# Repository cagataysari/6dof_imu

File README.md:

# README #

This is my hobby 6 DOF IMU project.
I am gonna add BOM list, pdf files later.

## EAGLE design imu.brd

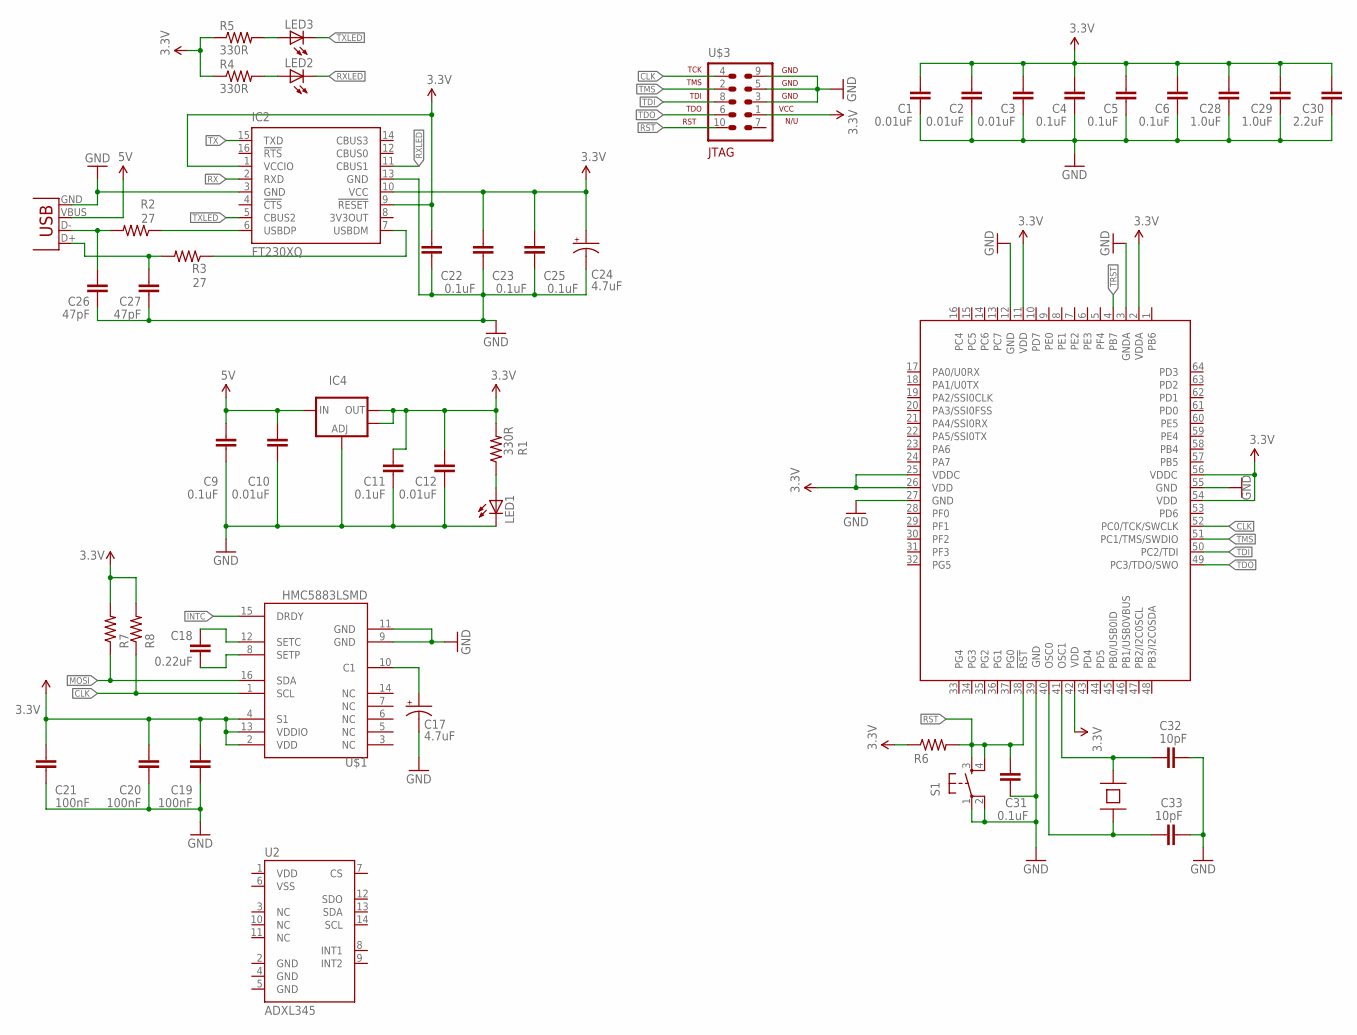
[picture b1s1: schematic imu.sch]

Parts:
C1, C2, C3, C10, C12: 0.01uF; 0603-CAP
C4, C5, C6, C9, C11, C22, C23, C25, C31: 0.1uF; 0603-CAP
C17, C24: 4.7uF; EIA3216
C18: 0.22uF; 0603-CAP
C19, C20, C21: 100nF; 0603-CAP
C26, C27: 47pF; 0603-CAP
C28, C29: 1.0uF; 0603-CAP
C30: 2.2uF; 0603-CAP
C32, C33: 10pF; 0603-CAP
IC1: TM4C123[6,F]XXPM; PM_S-PQFP-G64
IC2: FT230XQ; QFN16
IC4: V_REG_LM1117SOT223; SOT223
JP1: USBSMD; USB-MINIB
LED1, LED2, LED3: LED0603; LED-0603
R1: 330R; 0805
R2, R3: 27; 0603-RES
R4, R5: 330R; 0603-RES
R6, R7, R8: RESISTOR0603-RES; 0603-RES
S1: TAC_SWITCHSMD; TACTILE_SWITCH_SMD
U2: ADXL345; LGA14
U$1: HMC5883LSMD; 16LPCC
U$2: SMDCRYSTAL3225; IQG3225
U$3: ARM10JTAG; AVR-JTAG-10

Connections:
3.3V: C1.2, C2.2, C3.2, C4.2, C5.2, C6.2, C11.2, C12.2, C19.2, C20.2, C21.2, C22.2, C23.2, C24.A (+), C25.2, C28.2, C29.2, C30.2, IC1.2 (VDDA), IC1.11 (VDD), IC1.25 (VDDC), IC1.26 (VDD), IC1.42 (VDD), IC1.54 (VDD), IC1.56 (VDDC), IC2.1 (VCCIO), IC2.9 (!RESET), IC2.10 (VCC), IC4.2 (OUT), IC4.4 (OUT), R1.2, R4.1, R5.1, R6.1, R7.2, R8.2, U$1.2 (VDD), U$1.4 (S1), U$1.13 (VDDIO), U$3.1
5V: C9.2, C10.2, IC4.3 (IN), JP1.VBUS
CLK: IC1.52 (PC0/TCK/SWCLK), R8.1, U$1.1 (SCL), U$3.4
GND: C1.1, C2.1, C3.1, C4.1, C5.1, C6.1, C9.1, C10.1, C11.1, C12.1, C17.C (-), C19.1, C20.1, C21.1, C22.1, C23.1, C24.C (-), C25.1, C26.1, C27.1, C28.1, C29.1, C30.1, C31.1, C32.1, C33.2, IC1.3 (GNDA), IC1.12 (GND), IC1.27 (GND), IC1.39 (GND), IC1.55 (GND), IC2.3 (GND), IC2.13 (GND), IC4.1 (ADJ), JP1.GND, LED1.C, S1.1, S1.2, U$1.9 (GND), U$1.11 (GND), U$3.3, U$3.5, U$3.9
INTC: U$1.15 (DRDY)
MOSI: R7.1, U$1.16 (SDA)
unnamed: IC2.6 (USBDP), R2.1
unnamed: LED2.A, R4.2
unnamed: IC2.7 (USBDM), R3.1
unnamed: C26.2, JP1.D-, R2.2
unnamed: C17.A (+), U$1.10 (C1)
unnamed: C18.2, U$1.12 (SETC)
unnamed: C18.1, U$1.8 (SETP)
unnamed: C27.2, JP1.D+, R3.2
unnamed: LED3.A, R5.2
unnamed: C32.2, IC1.41 (OSC1), U$2.3
unnamed: C33.1, IC1.40 (OSC0), U$2.1
unnamed: LED1.A, R1.1
RST: C31.2, IC1.38 (!RST), R6.2, S1.3, S1.4, U$3.10
RX: IC2.2 (RXD)
RXLED: IC2.11 (CBUS1), LED2.C
TDI: IC1.50 (PC2/TDI), U$3.8
TDO: IC1.49 (PC3/TDO/SWO), U$3.6
TMS: IC1.51 (PC1/TMS/SWDIO), U$3.2
TRST: IC1.4 (PB7)
TX: IC2.15 (TXD)
TXLED: IC2.5 (CBUS2), LED3.C

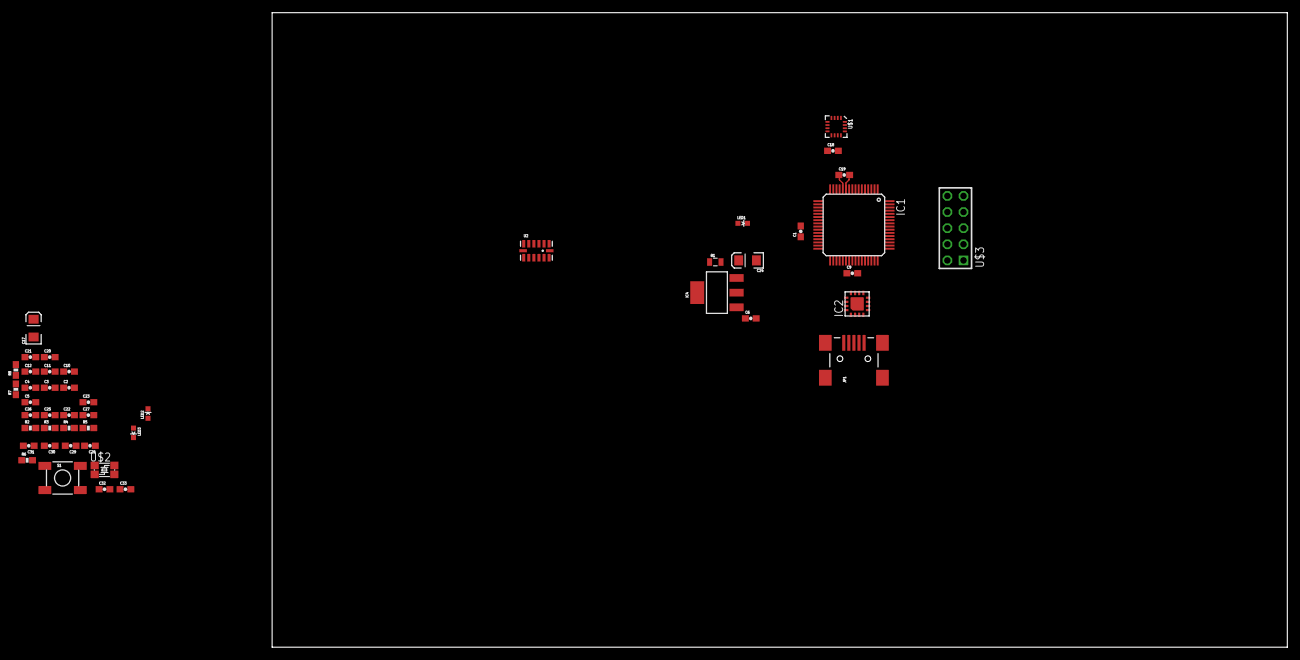
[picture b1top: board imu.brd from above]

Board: 4 copper layers, 160.0 x 100.0 mm, 47 parts (0 on the bottom side), 23 nets.

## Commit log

2016-01-02 Modification to schematics and board

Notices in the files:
parts and their libraries:
SparkFun-Passives: Licensing: CC v3.0 Share-Alike You are welcome to use this library for commercial purposes.
